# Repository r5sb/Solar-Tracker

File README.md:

# Solar-Tracker
Solar Tracker for my third year mini-project (2016) using an ATMega328.

Files included are:
<ul>
<li>Main board schematic.</li>
<li>Main board .brd file. (with custom 74AHC125N library)</li>
<li>LDR board schematic.</li>
<li>LDR board .brd file.</li>
<li>Main code.</li>
All schematics and board layouts are made in Eagle 7.2.0.

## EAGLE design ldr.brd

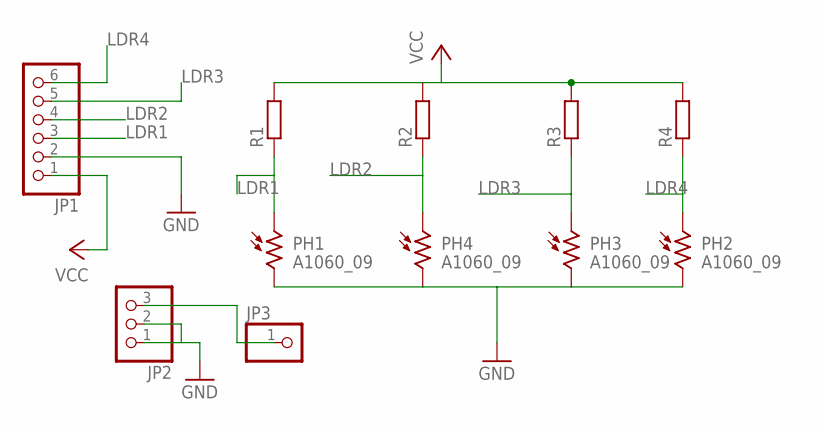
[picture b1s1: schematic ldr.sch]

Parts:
JP1: PINHD-1X6CB; 1X06-CLEANBIG
JP2: PINHD-1X3CB; 1X03-CLEANBIG
JP3: PINHD-1X1CB; 1X01-CLEANBIG
PH1, PH2, PH3, PH4: A1060_09; T0-46-A10XX
R1, R2, R3, R4: R-EU_0207/10; 0207/10

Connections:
GND: JP1.2, JP2.1, JP2.2, PH1.2, PH2.2, PH3.2, PH4.2
LDR1: JP1.3, PH1.1, R1.1
LDR2: JP1.4, PH4.1, R2.1
LDR3: JP1.5, PH3.1, R3.1
LDR4: JP1.6, PH2.1, R4.1
unnamed: JP2.3, JP3.1
VCC: JP1.1, R1.2, R2.2, R3.2, R4.2

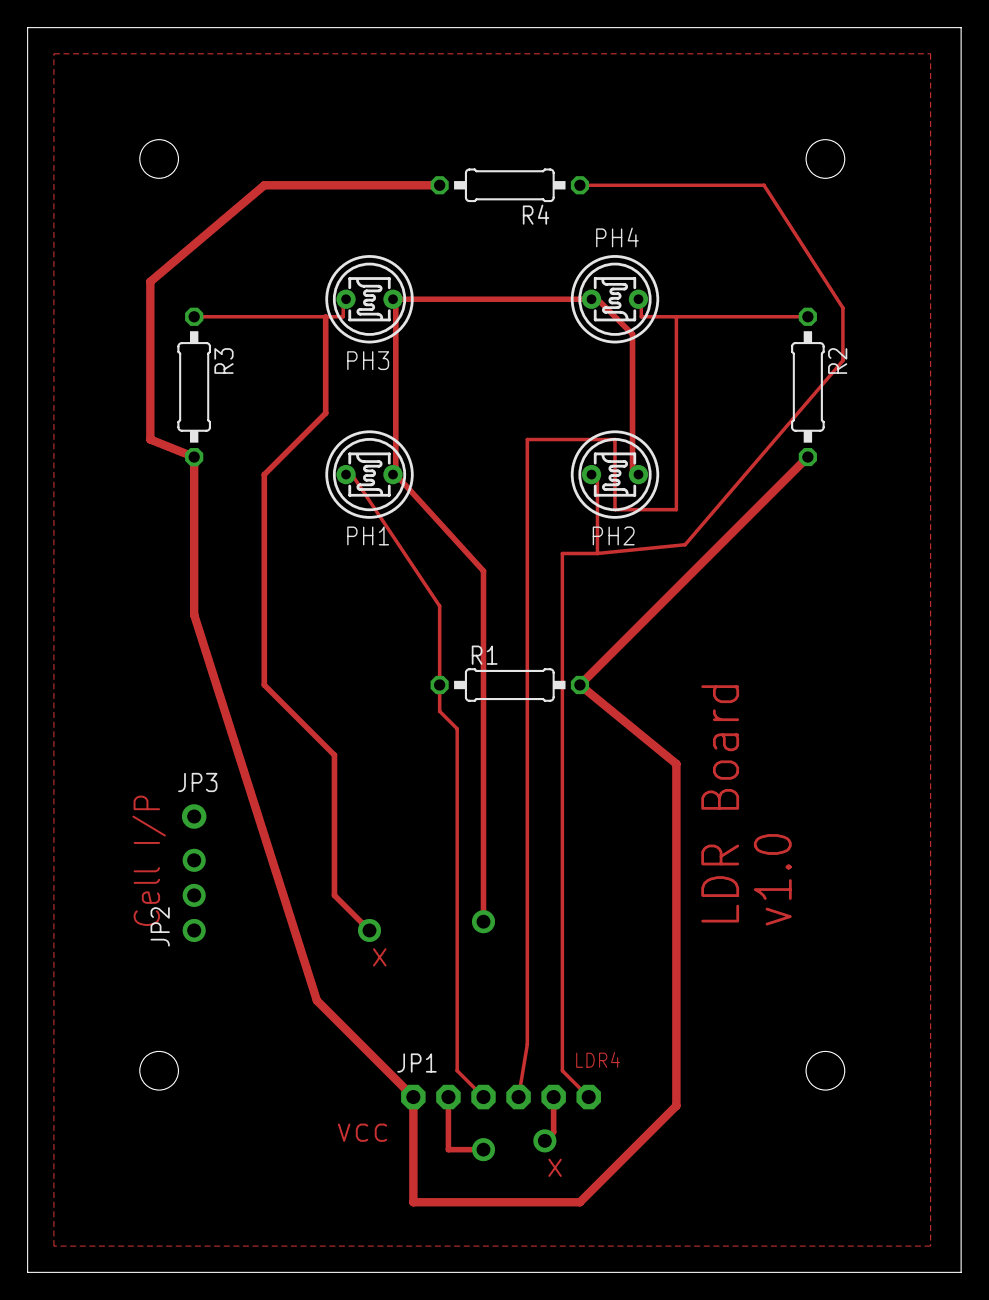
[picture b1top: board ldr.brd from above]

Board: 2 copper layers, 67.6 x 90.2 mm, 11 parts (0 on the bottom side), 7 nets.

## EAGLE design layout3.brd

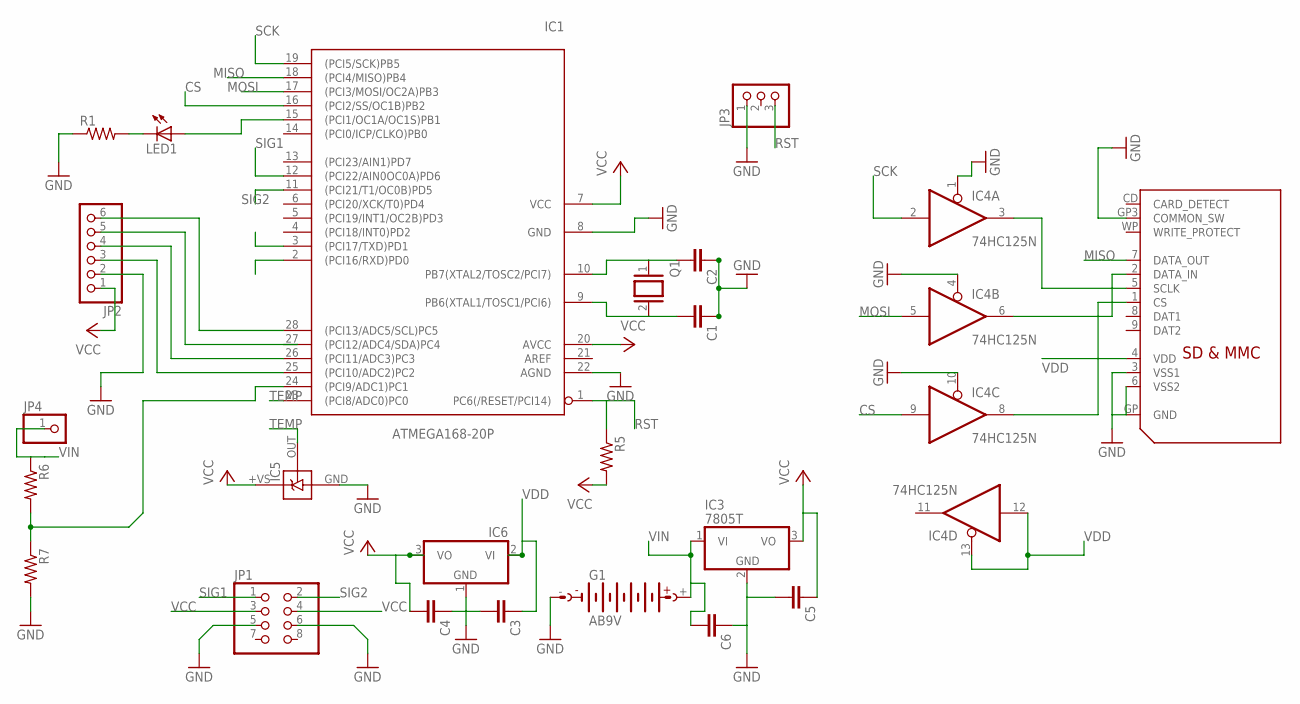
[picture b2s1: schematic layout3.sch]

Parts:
C1, C2, C3, C4, C5, C6: C-EU025-025X050; C025-025X050
G1: AB9V
IC1: ATMEGA168-20P; DIL28-3
IC3: 7805T; TO220H
IC4: 74HC125N; DIL14
IC5: LM35; TO-92-
IC6: 7906T; TO220H
JP1: PINHD-2X4; 2X04
JP2: PINHD-1X6CB; 1X06-CLEANBIG
JP3: PINHD-1X3CB; 1X03-CLEANBIG
JP4: PINHD-1X1CB; 1X01-CLEANBIG
LED1: LED5MM
Q1: XTAL/S; QS
R1, R5, R6, R7: R-US_0207/10; 0207/10
U$1: SDMMC06132; 06132

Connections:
CS: IC1.16 ((PCI2/SS/OC1B)PB2), IC4.9 (I)
GND: C1.1, C2.1, C3.2, C4.1, C5.2, C6.1, G1.-, IC1.8 (GND), IC1.22 (AGND), IC3.2 (GND), IC4.1 (OE), IC4.4 (OE), IC4.7 (GND), IC4.10 (OE), IC5.GND, IC6.1 (GND), JP1.5, JP1.6, JP2.2, JP3.1, R1.1, R7.2, U$1.3 (VSS1), U$1.6 (VSS2), U$1.GP (GND), U$1.GP3 (COMMON_SW)
MISO: IC1.18 ((PCI4/MISO)PB4), U$1.7 (DATA_OUT)
MOSI: IC1.17 ((PCI3/MOSI/OC2A)PB3), IC4.5 (I)
unnamed: C1.2, IC1.9 (PB6(XTAL1/TOSC1/PCI6)), Q1.2
unnamed: C2.2, IC1.10 (PB7(XTAL2/TOSC2/PCI7)), Q1.1
unnamed: IC1.28 ((PCI13/ADC5/SCL)PC5), JP2.6
unnamed: IC1.26 ((PCI11/ADC3)PC3), JP2.4
unnamed: IC1.27 ((PCI12/ADC4/SDA)PC4), JP2.5
unnamed: IC1.25 ((PCI10/ADC2)PC2), JP2.3
unnamed: IC4.6 (O), U$1.2 (DATA_IN)
unnamed: IC4.3 (O), U$1.5 (SCLK)
unnamed: IC4.8 (O), U$1.1 (CS)
unnamed: IC1.24 ((PCI9/ADC1)PC1), R6.2, R7.1
unnamed: LED1.K (C), R1.2
unnamed: IC1.15 ((PCI1/OC1A/OC1S)PB1), LED1.A
RST: IC1.1 (PC6(/RESET/PCI14)), JP3.3, R5.1
SCK: IC1.19 ((PCI5/SCK)PB5), IC4.2 (I)
SIG1: IC1.12 ((PCI22/AIN0OC0A)PD6), JP1.1
SIG2: IC1.11 ((PCI21/T1/OC0B)PD5), JP1.2
TEMP: IC1.23 ((PCI8/ADC0)PC0), IC5.OUT
VCC: C4.2, C5.1, IC1.7 (VCC), IC1.20 (AVCC), IC3.3 (VO), IC4.14 (VCC), IC5.+VS, IC6.3 (VO), JP1.3, JP1.4, JP2.1, R5.2
VDD: C3.1, IC4.12 (I), IC4.13 (OE), IC6.2 (VI), U$1.4 (VDD)
VIN: C6.2, G1.+, IC3.1 (VI), JP4.1, R6.1

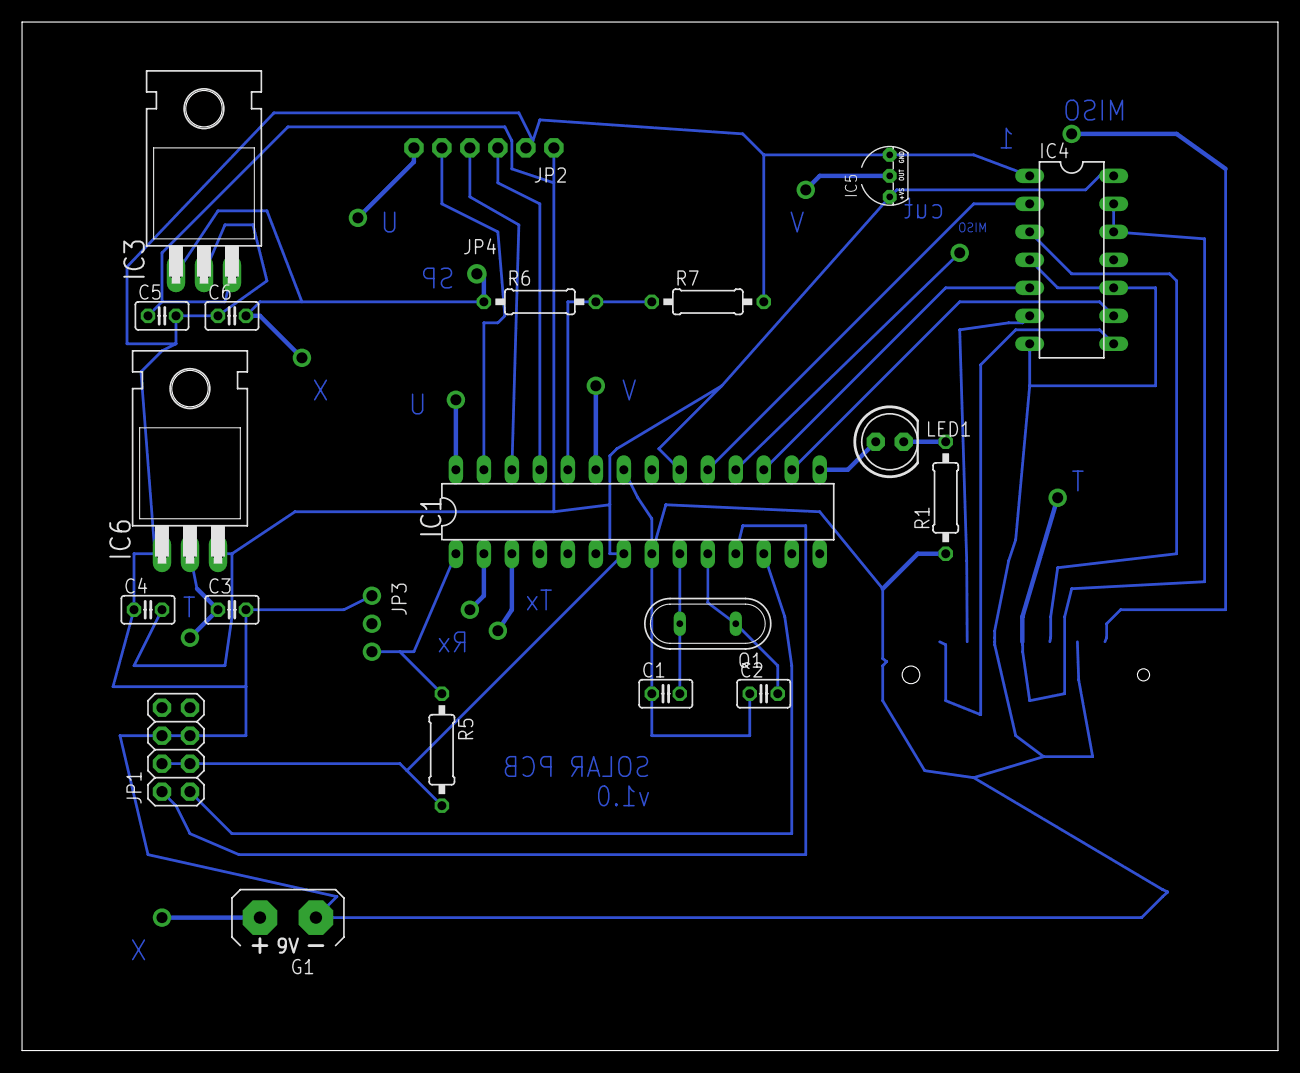
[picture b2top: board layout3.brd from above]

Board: 2 copper layers, 114.0 x 93.3 mm, 23 parts (1 on the bottom side), 24 nets.

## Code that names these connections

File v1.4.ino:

/**********************************************************************************
***********************************************************************************
***************Solar Tracker code for my Third Year Engineering Mini Project*******
***************Written by Sidharth Makhija on 7-Apr-2016***************************************
***************Code is provided AS-IS and under MIT Licence************************/

//Adding Libraries
#include <Servo.h>
#include <SPI.h>
#include <SD.h>

//Defining Variables and Pin Nos for LDRs, Temp Sensor and LED.
#define LDR1 A2
#define LDR2 A3
#define LDR3 A4
#define LDR4 A5
#define temp A0
#define led 9

const int chipSelect = 10;
String dataString = "";
int left=0;
int right=0;
int up=0;
int down=0;
int diffH=0;
int diffV=0;
int thresh=15;   // set threshold value to 15
int nthresh;
float val5=0;
float battV=0;

//Initializing Servos
Servo servoX;
Servo servoY;
int deg=0;

void setup()
{ 
Serial.begin(9600);
pinMode(led,OUTPUT);
pinMode(chipSelect,OUTPUT);
Serial.println("Setup");

//Assigning servos to pins 5,6. 
servoX.attach(6);
servoY.attach(5);

//Setting Y-axis to 90 
servoY.write(90);
//Stopping X-axis motor
servoX.write(83);
delay(1000);
//Setting Y-axis to 0
servoY.write(deg);
delay(20);

//Calling function to Initialize SD Card
InitializeSD();
dataString = "";//Readings to be written on SD Card go in this String
dataString="Temp and Solar Panel Readings";
//Calling function to write String to SD Card
writeSD(dataString);
Serial.println();
delay(3000); //wait 3 seconds
}

void loop()
{
dataString=""; //Emptying the String
takeReadings();//Calling function that takes readings and writes it to SD Card 
//Total delay = 1.15S (1150mS)

digitalWrite(led,LOW);
  
diffH=left-right; //Taking difference of Right and Left LDRs (X-axis) //-1*(right-left);
diffV=down-up;//Taking Difference of Up and Down LDRs (Y-axis) //-1*(up-down);
nthresh = -1*thresh; //negative threshold

Serial.print("DiffV= ");
Serial.println(diffV);
Serial.print("DiffH= ");
Serial.println(diffH);
Serial.println();

//For Y-axis
if(diffV>thresh) //if value is greater than threshold move up
{
  Serial.println("up");
  servoYup();// Calling function to turn Y-axis Servo up
}
else if(diffV<nthresh) //if value is lesser than negative threshold move down
{
 Serial.println("down"); // Calling function to turn Y-axis Servo down
 servoYdown();
}

//(For X-axis)
if(diffH>thresh) //if value is greater than threshold move right  
  {
   servoXRight(); //Calling Function to turn X-axis Servo right.
   Serial.println("right");
  }
else if(diffH<nthresh) //if value is less than negative threshold move left
  {
    servoXLeft(); //Calling function to turn X-axis Servo left.
    Serial.println("left");
  }
  
else
{
  servoX.write(83);//remain stationary
}
delay(1000);
}


//////////////////////////////FUNCTIONS//////////////////////////////////////////////////////

void servoYup()
{
   deg+=5; // Increment degree by 5
   servoY.write(deg);//Make Servo go to the assigned degree (clockwise)
   if(deg>=115) //If Servo reaches max limit
   {
     servoY.write(115);//keep servo in limit
   }
}

void servoYdown()
{
     deg-=5;//decrease degree by 5
     servoY.write(deg);//Make servo go to assigned degree
     if(deg<5)//If servo reaches minimum limit
     {
       servoY.write(5);//keep servo in limit
         
     }
}

void servoXRight()
{
  servoX.write(70);//Make servo turn to right
  delay(200);//keep on for 200mS
  servoX.write(83);//Stop servo
  delay(500);//keep off for 500mS
}

void servoXLeft()
{
   servoX.write(95);//Make servo turn left
  delay(200);//Keep on for 200mS
  servoX.write(83);//Stop servo
  delay(500);//Keep off for 500mS
}

void takeReadings()
{

digitalWrite(led,HIGH);
//Take Reading from Right LDR
right=map(analogRead(LDR1),0,1023,0,255); //Change range of LDR readings from 0-1023 to 0-255
Serial.print("right= ");
Serial.println(right);
delay(20);

//Take Reading from Left LDR
left=map(analogRead(LDR2),0,1023,0,255);
Serial.print("left= ");
Serial.println(left);
delay(20);

//Take Reading from Up LDR
up=map(analogRead(LDR3),0,1023,0,255);
Serial.print("up= ");
Serial.println(up);
delay(20);

//Take Reading from Down LDR
down=map(analogRead(LDR4),0,1023,0,255);
Serial.print("down= ");
Serial.println(down);
delay(20);
Serial.println();

//Take average reading of all LDR
int avg = (up+down+left+right)/4;
//Take percentage of sunlight available
float perc=(avg/255)*100;

//Add percentage sunlight to String
dataString+=String(perc);
dataString+="%";
dataString+=",";

//Take Temperature reading
val5=(5.0*analogRead(temp)*100.0)/1024;
delay(10);
val5=(5.0*analogRead(temp)*100.0)/1024;
delay(10);

//Add temperature to String
dataString+=String(val5);
dataString+=",";
Serial.print("Temp= ");
Serial.println(val5);
delay(20);

//Call Function to check voltage from solar panel
battV=batteryCheck();
delay(10);
battV=batteryCheck();

//Add solar panel Voltage to String
dataString+=String(battV);
Serial.print("Battery= ");
Serial.println(battV);
delay(20);

//Write all Data to the SD Card
writeSD(dataString);
delay(1000);
}

float batteryCheck()// Function to check voltage of Solar Panel
{
  //(val / resistorFactor) * referenceVolts*4; // calculate the ratio
  
  const float referenceVolts = 5;  // the default reference on a 5-volt board
//const float referenceVolts = 3.3;  // use this for a 3.3-volt board

const float R1 = 1000;//955 // value for a maximum voltage of 10 volts
const float R2 = 1000;//955
// determine by voltage divider resistors, see text
const float resistorFactor = 1023.0 / (R2/(R1 + R2));  
const int batteryPin = A1; // +V from battery is connected to analog pin 0
int val1 = analogRead(batteryPin);
delay(10);
int val2=analogRead(batteryPin);
float volts1 = val1*(5.0/1023.0)*2;
float volts2 = val2*(5.0/1023.0)*2;
if(volts1==volts2)
  {
    return volts1;
  }
else
  {
    volts2=volts2-volts1;
    volts1=volts1-volts2;
    return volts1;
  }
}

void InitializeSD()
{
   Serial.print("Initializing SD card...");
  // see if the card is present and can be initialized:
  if (!SD.begin(chipSelect)) 
  {
    Serial.println("Card failed, or not present");
    // don't do anything more:
    return;
  }
  Serial.println("card initialized.");
}

void writeSD(String a)
{
  File dataFile = SD.open("datalog.txt", FILE_WRITE);

  // if the file is available, write to it:
  if (dataFile) 
  {
    dataFile.println(a);
    dataFile.close();
    // print to the serial port too:
    Serial.println(a);
  }
  // if the file isn't open, pop up an error:
  else 
  {
    Serial.println("error opening datalog.txt");
  }
}

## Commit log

2016-04-22 Added files via upload
2016-05-07 Added files via upload
    Custom 74AHC125N library file (Eagle 7.2.0)
